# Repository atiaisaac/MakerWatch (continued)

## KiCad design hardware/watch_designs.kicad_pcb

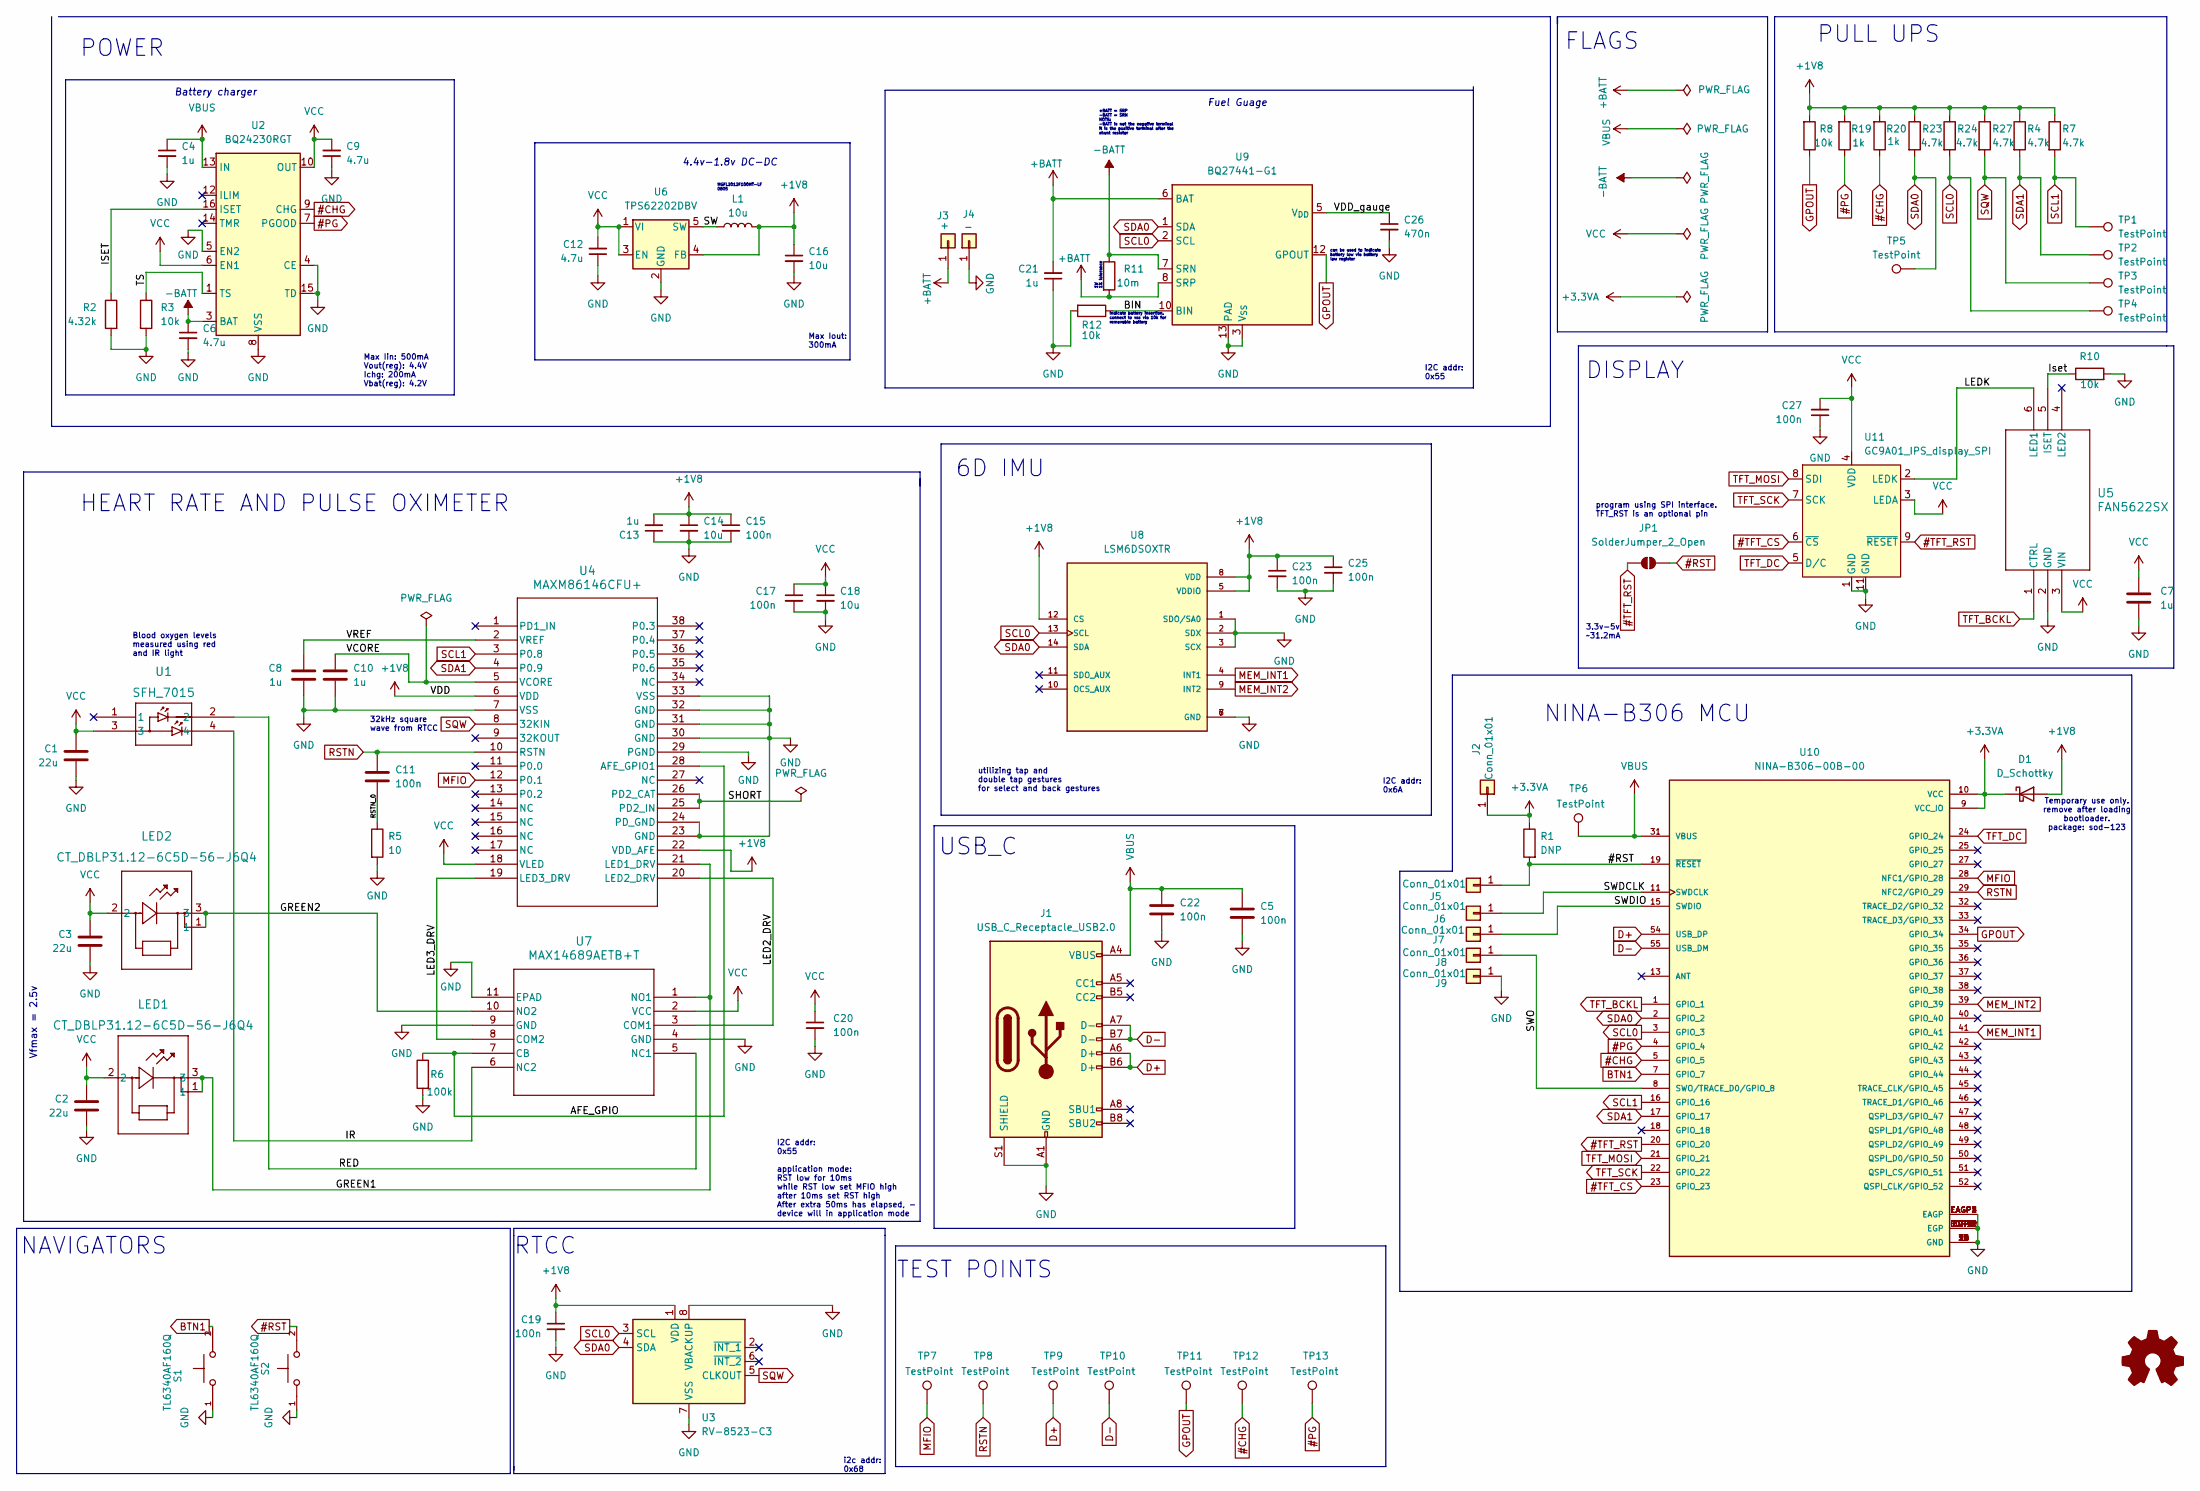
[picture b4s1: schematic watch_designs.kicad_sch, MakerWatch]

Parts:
C1, C2, C3: 22u; C_0603_1608Metric
C4, C7, C8, C10, C13, C21: 1u; C_0603_1608Metric
C5, C11, C15, C17, C19, C20, C22, C23, C25, C27: 100n; C_0603_1608Metric
C6, C9, C12: 4.7u; C_0603_1608Metric
C14, C16, C18: 10u; C_0603_1608Metric
C26: 470n; C_0603_1608Metric
D1: D_Schottky; D_SOD-123
J1: USB_C_Receptacle_USB2.0; USB_C_Receptacle_GCT_USB4105-xx-A_16P_TopMnt_Horizontal
J2, J5, J6, J7, J8, J9: Conn_01x01; SolderWirePad_1x01_SMD_1x2mm
J3: +; SolderWirePad_1x01_SMD_1x2mm
J4: -; SolderWirePad_1x01_SMD_1x2mm
JP1: SolderJumper_2_Open; SolderJumper-2_P1.3mm_Open_RoundedPad1.0x1.5mm
L1: 10u; L_0805_2012Metric
LED1, LED2: CT_DBLP31.12-6C5D-56-J6Q4; CT DBLP31.12-6C5D-56-J6Q4_OSR
R1: DNP; R_0603_1608Metric
R2: 4.32k; R_0603_1608Metric
R3, R8, R10, R12: 10k; R_0603_1608Metric
R4, R7, R23, R24, R27: 4.7k; R_0603_1608Metric
R5: 10; R_0603_1608Metric
R6: 100k; R_0603_1608Metric
R11: 10m; R_1206_3216Metric
R19, R20: 1k; R_0603_1608Metric
S1, S2: TL6340AF160Q; SW_TL6340AF160Q; PARTREV 10.23.2019
TP1, TP2, TP3, TP4, TP5, TP6, TP7, TP8, TP9, TP10, TP11, TP12, TP13: TestPoint; TestPoint_Pad_D1.0mm
U1: SFH_7015; SFH 7015_OSR
U2: BQ24230RGT; VQFN-16-1EP_3x3mm_P0.5mm_EP1.68x1.68mm_ThermalVias
U3: RV-8523-C3; RTC_SMD_MicroCrystal_C3_2.5x3.7mm
U4: MAXM86146CFU+; 21-100323A_90-100112A_MXM
U5: FAN5622SX; SSOT6_3X1P7_ONS
U6: TPS62202DBV; SOT-23-5
U7: MAX14689AETB+T; 21-100013A_T102A2&plus_2C_MXM-L
U8: LSM6DSOXTR; PQFN50P250X300X86-14N; PARTREV 3.0
U9: BQ27441-G1; Texas_S-PDSO-N12
U10: NINA-B306-00B-00; XCVR_NINA-B306-00B-00; PARTREV R07
U11: GC9A01_IPS_display_SPI; 15p_tft_P0.5

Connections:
#CHG: R20.1, TP12.1, U2.9 (CHG), U10.5 (GPIO_5)
#PG: R19.1, TP13.1, U2.7 (PGOOD), U10.4 (GPIO_4)
#RST: J5.1, JP1.2 (B), R1.2, S2.2, U10.19 (~RESET)
#TFT_CS: U10.23 (GPIO_23), U11.6 (~CS)
#TFT_RST: JP1.1 (A), U10.20 (GPIO_20), U11.9 (~RESET)
+1V8: C13.2, C14.1, C15.1, C16.1, C19.1, C23.1, C25.1, D1.2 (A), L1.2, R4.1, R7.1, R8.2, R19.2, R20.2, R23.1, R24.1, R27.1, U3.1 (VDD), U4.6 (VDD), U4.22 (VDD_AFE), U6.4 (FB), U8.5 (VDDIO), U8.8 (VDD), U8.12 (CS)
+3.3VA: D1.1 (K), J2.1, R1.1, U10.9 (VCC_IO), U10.10 (VCC)
+BATT: C21.2, J3.1, R11.2, U9.6 (BAT), U9.8 (SRP)
-BATT: C6.1, R11.1, U2.2 (BAT), U2.3 (BAT), U9.7 (SRN)
/AFE_GPIO: R6.1, U4.28 (AFE_GPIO1), U7.7 (CB)
/BIN: R12.1, U9.10 (BIN)
/GREEN1: LED1.1, LED1.3, U4.21 (LED1_DRV), U7.1 (NO1)
/GREEN2: LED2.1, LED2.3, U7.10 (NO2)
/IR: U1.4, U7.6 (NC2)
/ISET: R2.1, U2.16 (ISET)
/Iset: R10.1, U5.5 (ISET)
/LED2_DRV: U4.20 (LED2_DRV), U7.3 (COM1)
/LED3_DRV: U4.19 (LED3_DRV), U7.8 (COM2)
/LEDK: U5.6 (LED1), U11.2 (LEDK)
/RED: U1.2, U7.5 (NC1)
/RSTN_0: C11.2, R5.1
/SHORT: U4.25 (PD2_IN), U4.26 (PD2_CAT)
/SW: L1.1, U6.5 (SW)
/SWDCLK: J6.1, U10.11 (SWDCLK)
/SWDIO: J7.1, U10.15 (SWDIO)
/SWO: J8.1, U10.8 (SWO/TRACE_D0/GPIO_8)
/TS: R3.1, U2.1 (TS)
/VCORE: C10.1, U4.5 (VCORE)
/VDD_gauge: C26.1, U9.5 (V_{DD})
/VREF: C8.2, U4.2 (VREF)
BTN1: S1.2, U10.7 (GPIO_7)
D+: J1.A6 (D+), J1.B6 (D+), TP9.1, U10.54 (USB_DP)
D-: J1.A7 (D-), J1.B7 (D-), TP10.1, U10.55 (USB_DM)
GND: C1.1, C2.1, C3.1, C4.2, C5.2, C6.2, C7.2, C8.1, C9.1, C10.2, C12.1, C13.1, C14.2, C15.2, C16.2, C17.2, C18.2, C19.2, C20.2, C21.1, C22.2, C23.2, C25.2, C26.2, C27.1, J1.A1 (GND), J1.A12 (GND), J1.B1 (GND), J1.B12 (GND), J1.S1 (SHIELD), J4.1, J9.1, R2.2, R3.2, R5.2, R6.2, R10.2, R12.2, S1.1, S2.1, U2.4 (CE), U2.5 (EN2), U2.8 (VSS), U2.15 (TD), U2.17 (VSS), U3.7 (VSS), U3.8 (VBACKUP), U4.7 (VSS), U4.23 (GND), U4.24 (PD_GND), U4.29 (PGND), U4.30 (GND), U4.31 (GND), U4.32 (GND), U4.33 (VSS), U5.2 (GND), U6.2 (GND), U7.4 (GND), U7.9 (GND), U7.11 (EPAD), U8.1 (SDO/SA0), U8.2 (SDX), U8.3 (SCX), U8.6 (GND), U8.7 (GND), U9.3 (V_{SS}), U9.13 (PAD), U10.6 (GND), U10.12 (GND), U10.14 (GND), U10.26 (GND), U10.30 (GND), U10.53 (GND), U10.EAGP1 (EAGP), U10.EAGP2 (EAGP), U10.EAGP3 (EAGP), U10.EAGP4 (EAGP), U10.EGP1 (EGP), U10.EGP2 (EGP), U10.EGP3 (EGP), U10.EGP4 (EGP), U10.EGP5 (EGP), U10.EGP6 (EGP), U10.EGP7 (EGP), U10.EGP8 (EGP), U10.EGP9 (EGP), U10.EGP10 (EGP), U10.EGP11 (EGP), U10.EGP12 (EGP), U11.1 (GND), U11.11 (GND)
GPOUT: R8.1, TP11.1, U9.12 (GPOUT), U10.34 (GPIO_34)
MEM_INT1: U8.4 (INT1), U10.41 (GPIO_41)
MEM_INT2: U8.9 (INT2), U10.39 (GPIO_39)
MFIO: TP7.1, U4.12 (P0.1), U10.28 (NFC1/GPIO_28)
RSTN: C11.1, TP8.1, U4.10 (RSTN), U10.29 (NFC2/GPIO_29)
SCL0: R24.2, TP4.1, U3.3 (SCL), U8.13 (SCL), U9.2 (SCL), U10.3 (GPIO_3)
SCL1: R7.2, TP1.1, U4.3 (P0.8), U10.16 (GPIO_16)
SDA0: R23.2, TP5.1, U3.4 (SDA), U8.14 (SDA), U9.1 (SDA), U10.2 (GPIO_2)
SDA1: R4.2, TP2.1, U4.4 (P0.9), U10.17 (GPIO_17)
SQW: R27.2, TP3.1, U3.5 (CLKOUT), U4.8 (32KIN)
TFT_BCKL: U5.1 (CTRL), U10.1 (GPIO_1)
TFT_DC: U10.24 (GPIO_24), U11.5 (D/C)
TFT_MOSI: U10.21 (GPIO_21), U11.8 (SDI)
TFT_SCK: U10.22 (GPIO_22), U11.7 (SCK)
VBUS: C4.1, C5.1, C22.1, J1.A4 (VBUS), J1.A9 (VBUS), J1.B4 (VBUS), J1.B9 (VBUS), TP6.1, U2.13 (IN), U10.31 (VBUS)
VCC: C1.2, C2.2, C3.2, C7.1, C9.2, C12.2, C17.1, C18.1, C20.1, C27.2, LED1.2, LED2.2, U1.3, U2.6 (EN1), U2.10 (OUT), U2.11 (OUT), U4.18 (VLED), U5.3 (VIN), U6.1 (VI), U6.3 (EN), U7.2 (VCC), U11.3 (LEDA), U11.4 (VDD)

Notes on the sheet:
3.3v-5v ~31.2mA
NAVIGATORS
RTCC
utilizing tap and double tap gestures for select and back gestures
DISPLAY
4.4v-1.8v DC-DC
i2c addr: 0x68
program using SPI interface. TFT_RST is an optional pin
1W 1% tolerance
I2C addr: 0x6A
USB_C
Blood oxygen levels measured using red and IR light
HEART RATE AND PULSE OXIMETER
POWER
indicate battery insertion. connect to vss via 10k for removable battery
MGFL2012F100MT-LF 0805
6D IMU
FLAGS
TEST POINTS
PULL UPS
Fuel Guage
Battery charger
NINA-B306 MCU
I2C addr: 0x55 application mode: RST low for 10ms while RST low set MFIO high after 10ms set RST high After extra 50ms has elapsed, - device will in application mode
32kHz square wave from RTCC
Max Iout: 300mA
Max Iin: 500mA Vout(reg): 4.4V Ichg: 200mA Vbat(reg): 4.2V
Temporary use only. remove after loading bootloader. package: sod-123
can be used to indicate battery low via battery low register
+BATT = SRP -BATT = SRN NOTE: -BATT is not the negative terminal it is the positive terminal after the shunt resistor
I2C addr: 0x55
Vfmax = 2.5v

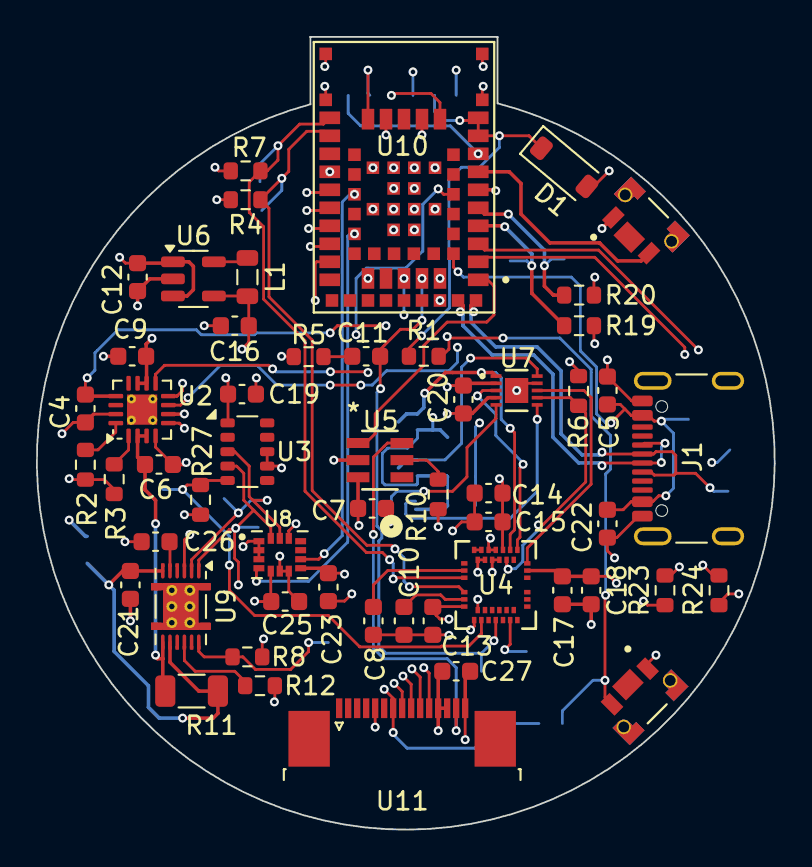
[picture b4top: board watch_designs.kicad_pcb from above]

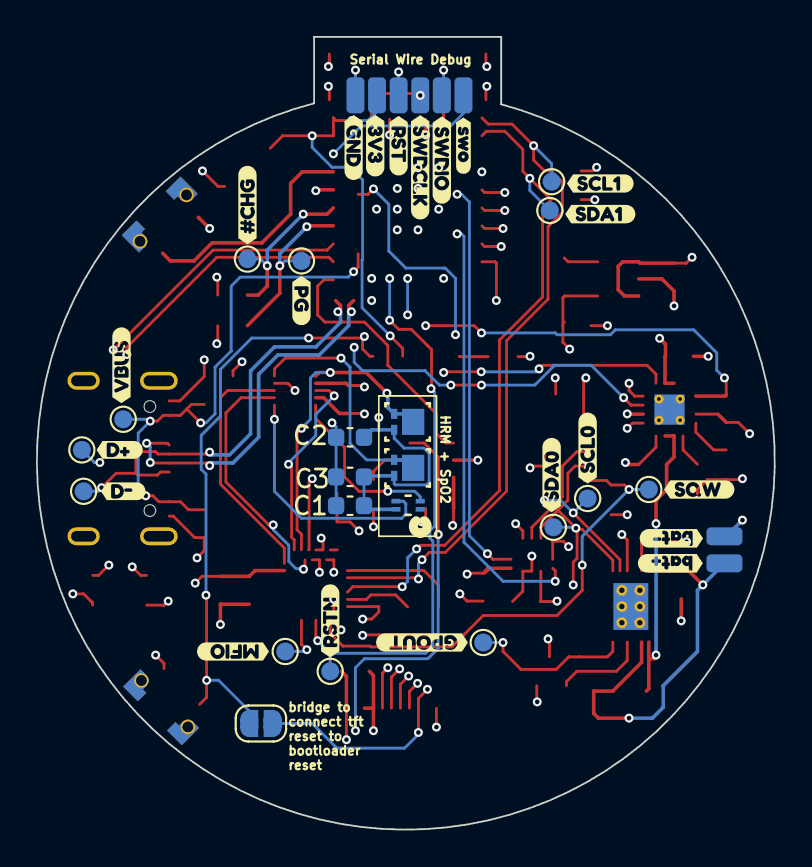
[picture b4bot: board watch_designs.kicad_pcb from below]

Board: 6 copper layers, 41.0 x 44.0 mm, 103 parts (49 on the bottom side), 50 nets.

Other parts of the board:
kibuzzard-6701C6B8: G***; kibuzzard-6701C6B8
kibuzzard-6701C68B: G***; kibuzzard-6701C68B
kibuzzard-6701EF64: G***; kibuzzard-6701EF64
kibuzzard-6701EFA6: G***; kibuzzard-6701EFA6
kibuzzard-6701EFE1: G***; kibuzzard-6701EFE1
kibuzzard-6701F00D: G***; kibuzzard-6701F00D
kibuzzard-6701F1A2: G***; kibuzzard-6701F1A2
kibuzzard-6701F1B6: G***; kibuzzard-6701F1B6
kibuzzard-6701F1DA: G***; kibuzzard-6701F1DA
kibuzzard-6701F2EA: G***; kibuzzard-6701F2EA
kibuzzard-6701F2FC: G***; kibuzzard-6701F2FC
kibuzzard-6701F028: G***; kibuzzard-6701F028
kibuzzard-6701F046: G***; kibuzzard-6701F046
kibuzzard-6707C4A8: G***; kibuzzard-6707C4A8
kibuzzard-6707C4C8: G***; kibuzzard-6707C4C8
kibuzzard-6707C4D5: G***; kibuzzard-6707C4D5
kibuzzard-6707C4E9: G***; kibuzzard-6707C4E9
kibuzzard-6707C492: G***; kibuzzard-6707C492
kibuzzard-6707C511: G***; kibuzzard-6707C511
kibuzzard-6707D37A: G***; kibuzzard-6707D37A
kibuzzard-6707D367: G***; kibuzzard-6707D367

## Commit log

2023-11-25 Added datasheets
2024-10-12 uploaded datasheets folder
2024-10-12 added kicad files
2024-10-12 added images
2024-11-07 Updated README.md to include display driver type
2025-06-29 image of new updated design
2025-07-01 updated design
2025-07-01 made design changes
2025-12-27 deleting all files
2025-12-27 restructured project files
2025-12-27 added kicad custom library as submodule
2025-12-27 updated design files with appropriate parts
2025-12-27 updated devicetree to include rtcc button
2026-01-09 restructured files
2026-04-13 updated design as a two part pcb
2026-04-19 updated design to include two boards connected back to back
2026-04-26 two seperate projects for watch main board and ppg attachment
2026-05-17 updated designs
2026-05-17 added images of new design
2026-05-17 updated readme.md file
